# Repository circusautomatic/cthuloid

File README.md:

# cthuloid

Cthuloid is an experimental autonomous theater umbrella project by Circus Automatic.

build a theater system that integrates robotics and performance into a hackable physical space where the performer can dictate lighting design to follow their every movement. Future plans include sound integration, shape changing scenery and more.

Inspired largely by video game level design, it will use blender and other programs for its internal representation. low cost electronics / sensors will be crafted for its real world implementation. a big goal is to form the feedback loop which will allow for more dynamic performance possibilities.
---

Folders of note:
- ### LightArm 
*-ethernet-enabled spotlight robot project*
- ### Arduino/LightArm 
*-firware for the spotlight robot*
- ### Arduino/LEDController  
*-firmware for ethernet-enabled controller for LEDs at high resolution*
- ### ghettopticon 
*-humanoid robot mounted on a motorized wheelchair (should be moved to its own repo)*

## License

Not yet declared.

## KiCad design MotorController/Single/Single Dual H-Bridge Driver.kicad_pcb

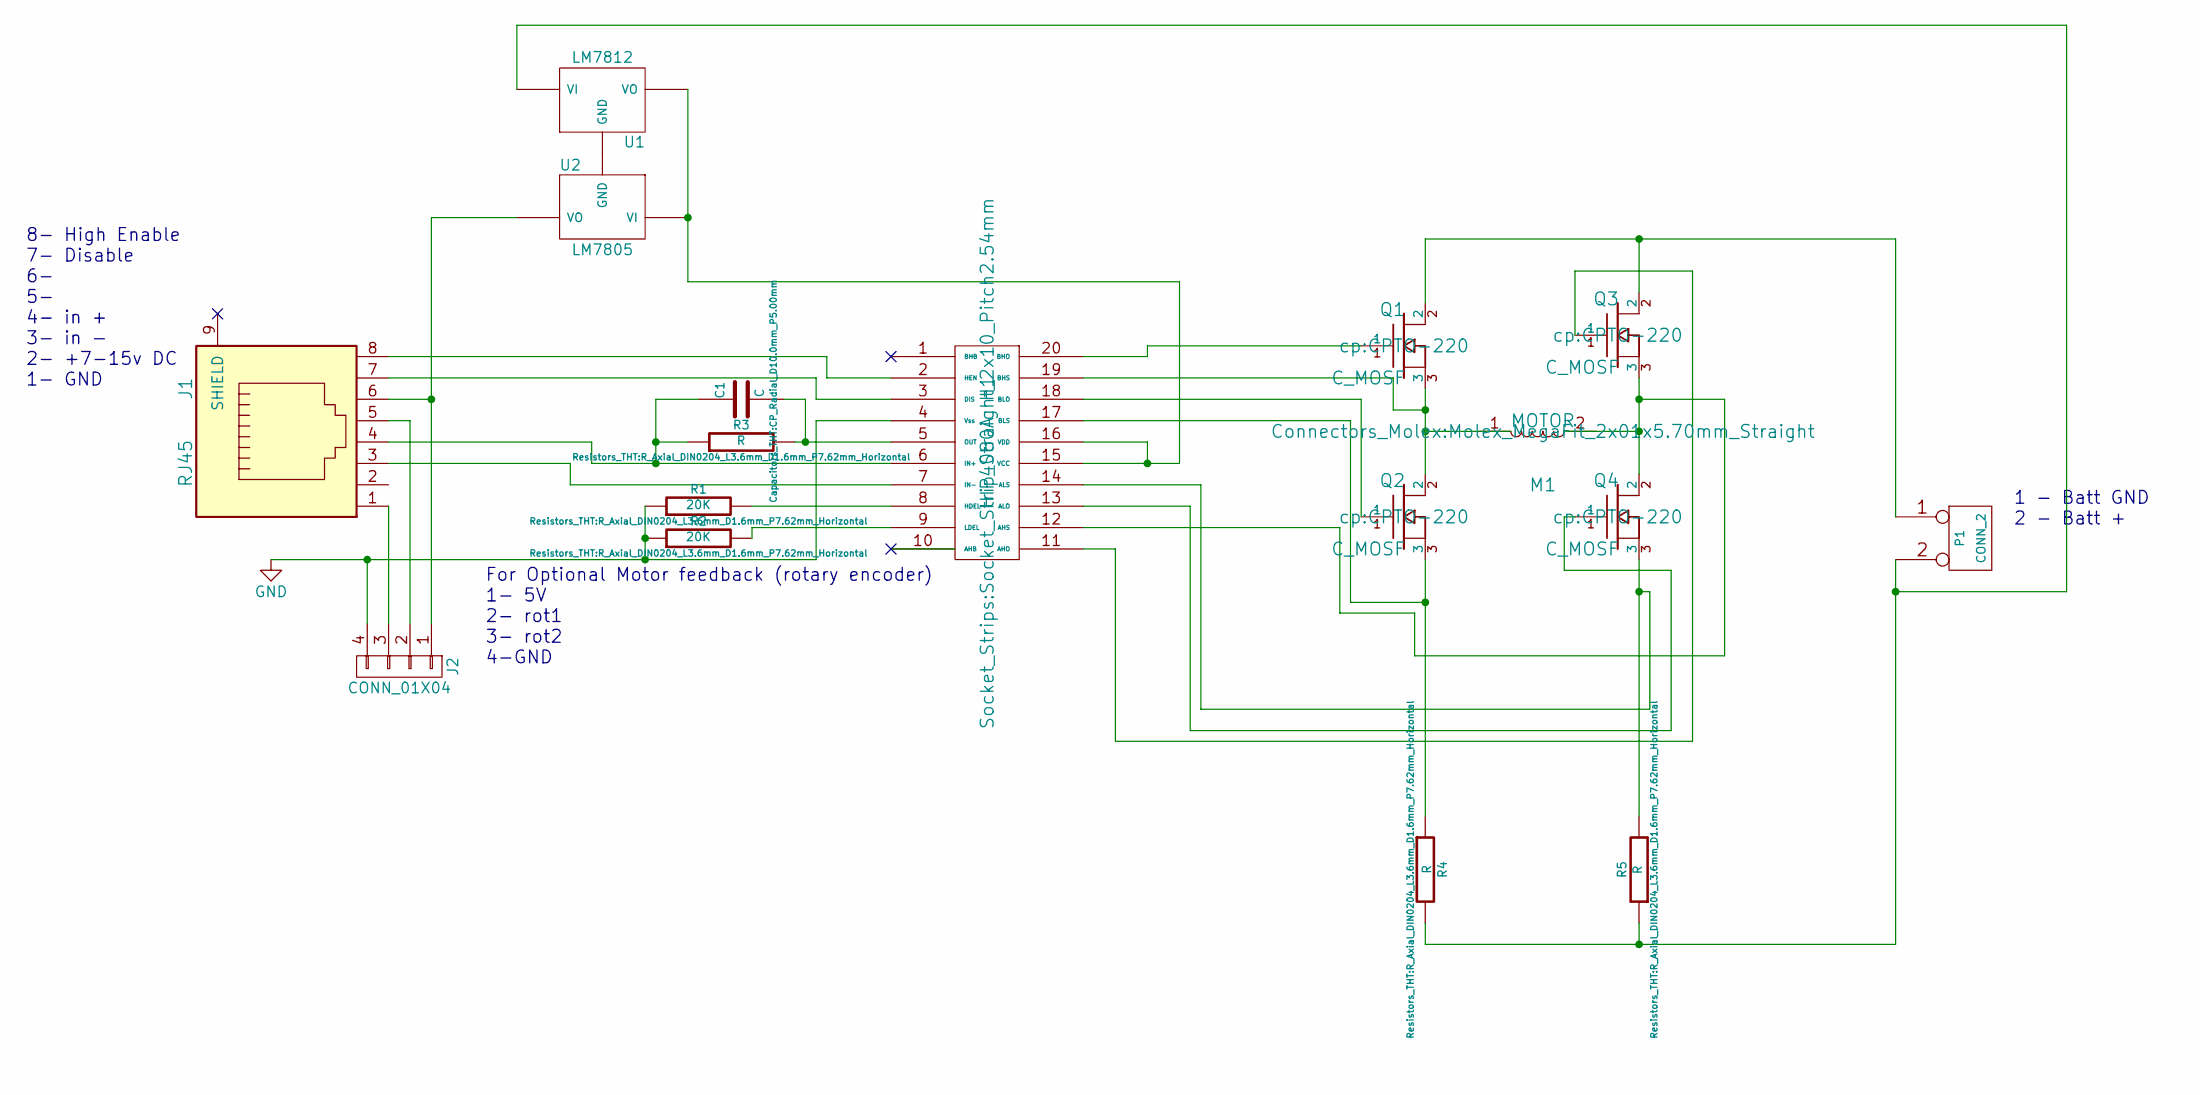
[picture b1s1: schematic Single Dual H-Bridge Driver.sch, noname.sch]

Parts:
C1: C; CP_Radial_D10.0mm_P5.00mm
H1: HIP4080A; Socket_Strip_Straight_2x10_Pitch2.54mm
J1: RJ45; RJ45_8
J2: CONN_01X04; JST_EH_B04B-EH-A_04x2.50mm_Straight
M1: MOTOR; Molex_MegaFit_2x01x5.70mm_Straight
P1: CONN_2; Molex_MegaFit_2x01x5.70mm_Straight
Q1, Q2, Q3, Q4: C_MOSF; CPTO-220
R1, R2: 20K; R_Axial_DIN0204_L3.6mm_D1.6mm_P7.62mm_Horizontal
R3, R4, R5: R; R_Axial_DIN0204_L3.6mm_D1.6mm_P7.62mm_Horizontal
U1: LM7812; CPTO-220
U2: LM7805; CPTO-220

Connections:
GND: H1.4 (Vss), J2.4, R1.1, R2.1
unnamed: C1.1, H1.6 (IN+), J1.4, R3.1
unnamed: C1.2, H1.5 (OUT), R3.2
unnamed: H1.2 (HEN), J1.8
unnamed: H1.3 (DIS), J1.7
unnamed: H1.7 (IN-), J1.3
unnamed: H1.8 (HDEL), R1.2
unnamed: H1.9 (LDEL), R2.2
unnamed: H1.11 (AHO), Q3.1
unnamed: H1.12 (AHS), M1.2, Q3.3, Q4.2
unnamed: H1.13 (ALO), Q4.1
unnamed: H1.14 (ALS), Q4.3, R5.2
unnamed: H1.15 (VCC), H1.16 (VDD), U1.VO, U2.VI
unnamed: H1.17 (BLS), Q2.3, R4.1
unnamed: H1.18 (BLO), Q2.1
unnamed: H1.19 (BHS), M1.1, Q1.3, Q2.2
unnamed: H1.20 (BHO), Q1.1
unnamed: J1.1, J2.3
unnamed: J1.5, J2.2
unnamed: J1.6, J2.1, U2.VO
unnamed: P1.1, Q1.2, Q3.2
unnamed: P1.2 (PM), R4.2, R5.1, U1.VI
unnamed: U1.GND, U2.GND

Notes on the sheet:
8- High Enable 7- Disable 6- 5- 4- in + 3- in - 2- +7-15v DC 1- GND
1 - Batt GND 2 - Batt +
For Optional Motor feedback (rotary encoder) 1- 5V 2- rot1 3- rot2 4-GND

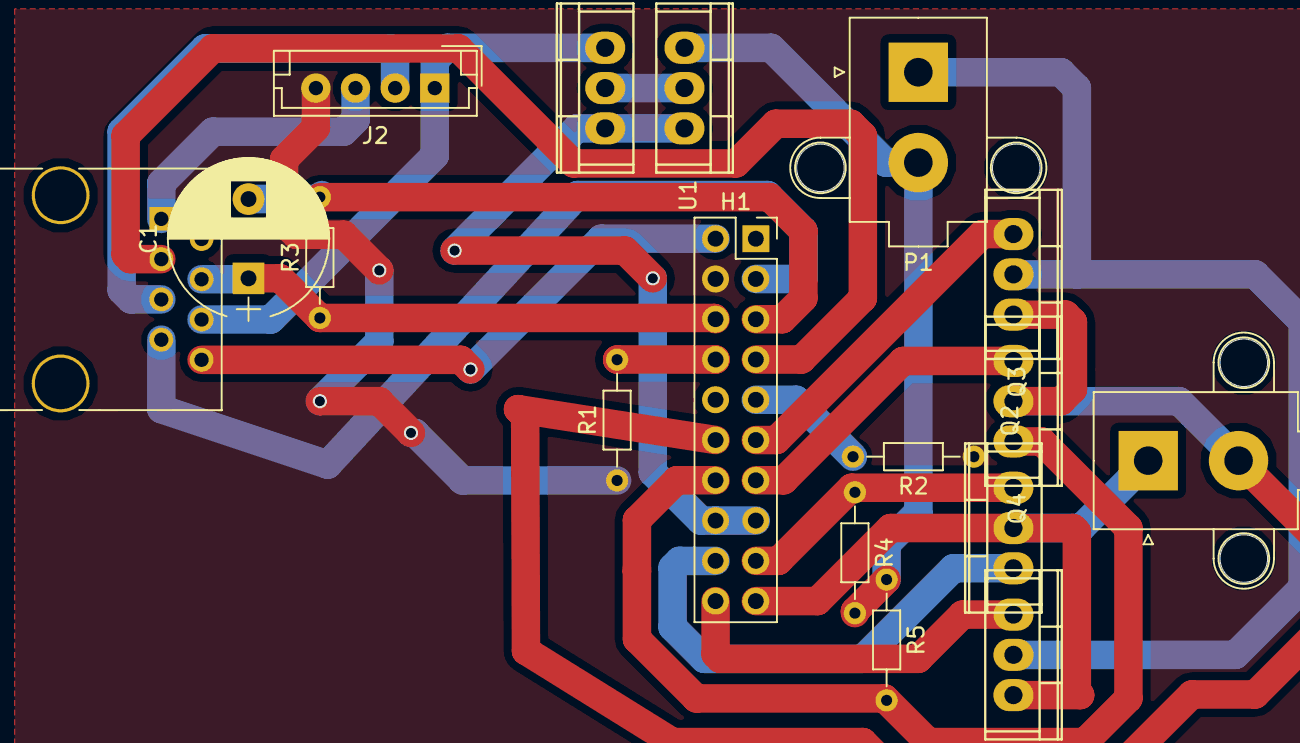
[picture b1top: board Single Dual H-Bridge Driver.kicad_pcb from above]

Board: 2 copper layers, 17 parts (0 on the bottom side), 23 nets.

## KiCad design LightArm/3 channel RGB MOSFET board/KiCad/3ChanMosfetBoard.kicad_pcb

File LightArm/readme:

An ethernet-enabled LED spotlight robot with Dynamixel servos and 3D printed parts.

The controller for this robot listens for TCP/IP connections on port 1337, supports multiple connections, and speaks a human-readable protocol with instructive error messages. It runs on an Arduino Mega and communicates with Dynamixel servos via USART.

Blender is used as a modeling and simulation environment. The robot can be animated or controlled in real-time. To do this, you must put the IP address of the robot in the model name, run the robot_panel.py script, and then turn Animation mode.

Controlling the robot is as simple as telneting to it. IP properties are settable and stored in EEPROM. Mac address is assigned based on the IP address. DHCP is not supported only because of the difficulties of not using static IPs.

In this repo:
android - a simple android program to control movement of two LightArms
blender - Blender models and python integration for controlling LightArms
python - useful standalone scripts
LED MOSFET board.fzz - a schematic of the LED driver

(firmware is located in /Arduino)

Components:
- 2 Dynamixel servos
- 100 Watt LED, heatsink, and fan
- custom LED driver
- Arduino Mega and ethernet module
- 12 Volt power supply (Wattage?)
- step-up power converter (to 33 Volts)

Getting Started:
- telnet to the lightarm on port 1337. Default IPv4 address is 10.0.2.255; see /Arduino/LightArm/LightArm.ino. There is no greeting upon connection, due to the nature of the Arduino ethernet library. Once connected, type the following commands and hit enter after each one.
- r
- p <1-5>
- pwm <0-65535>

Commands:
plevel - see or change the amount of text sent in response to a command
pwm - change LED brightness
v - check first servo voltage
r - report servo positions
s - change servo positions
p - choose preset position of servos
speed - see or change servo speed
relax - relax servos so they can be manually positioned
torq - un-relax some or all servos
circle - perform a circle in the plane perpendicular to neutral
id - change an internal servo ID
ip - change static IP address
gateway - change gateway address
port - change listening port
restart - restart network module to use new settings
clear - clear saved settings (just network settings for now)

TODO:
- modify ethernet library to greet client upon connection
- support DHCP and figure out how to identify individual robots
- add option for network security (so a person cannot just telnet into the robot)

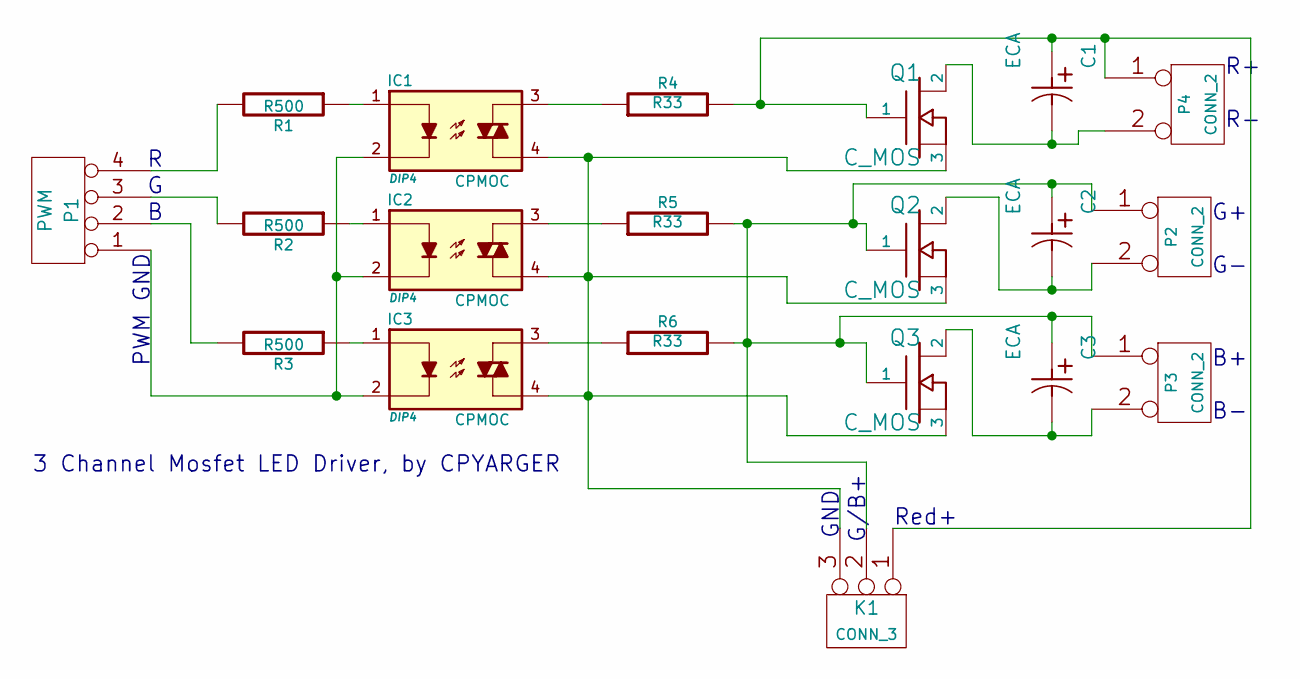
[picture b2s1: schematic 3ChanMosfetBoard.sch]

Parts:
C1, C2, C3: ECA
IC1, IC2, IC3: CPMOC; DIP4
K1: CONN_3
P1: PWM
P2, P3, P4: CONN_2
Q1, Q2, Q3: C_MOS
R1, R2, R3: R500
R4, R5, R6: R33

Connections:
unnamed: C2.2, P2.2 (PM), Q2.2
unnamed: C3.2, P3.2 (PM), Q3.2
unnamed: C1.2, P4.2 (PM), Q1.2
unnamed: IC2.1, R2.1
unnamed: IC3.1, R3.1
unnamed: IC1.1, R1.1
unnamed: IC1.3, R4.1
unnamed: IC1.2, IC2.2, IC3.2, P1.1
unnamed: IC2.3, R5.1
unnamed: IC3.3, R6.1
unnamed: C2.1, C3.1, K1.2 (PM), P2.1, P3.1, Q2.1, Q3.1, R5.2, R6.2
unnamed: C1.1, K1.1, P4.1, Q1.1, R4.2
unnamed: P1.2, R3.2
unnamed: P1.3, R2.2
unnamed: P1.4, R1.2
unnamed: IC1.4, IC2.4, IC3.4, K1.3, Q1.3, Q2.3, Q3.3

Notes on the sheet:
GND
Red+
G/B+
PWM GND
3 Channel Mosfet LED Driver, by CPYARGER

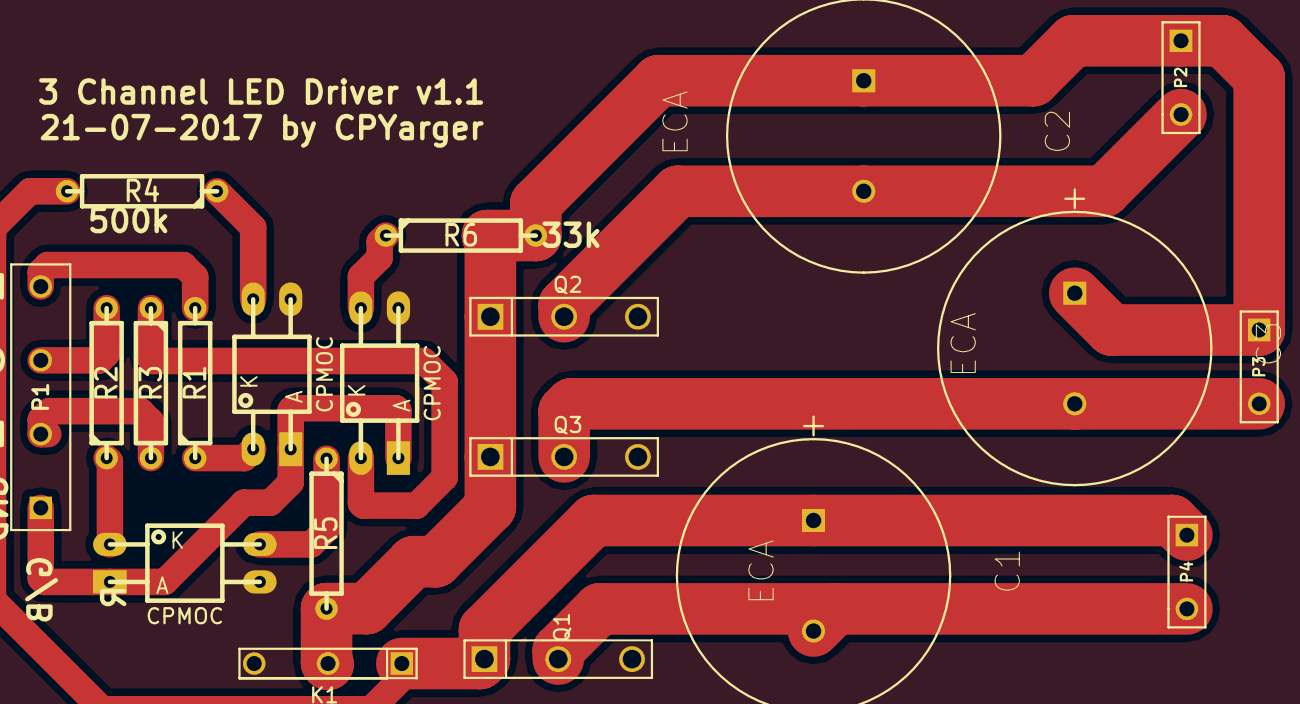
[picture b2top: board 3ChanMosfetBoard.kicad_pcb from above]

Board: 2 copper layers, 20 parts (0 on the bottom side), 16 nets.

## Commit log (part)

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2016-03-24 android app to control light arms
2016-03-25 demo app
2016-06-07 adding in models
2016-06-07 reorg
2016-06-08 adding in ik axis constraints to bones, and also a new bone for the ik which is a target bone, also a track to constraint and a location constraint on the target bone for the ik chain so that it all 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
2016-06-09 voyeur handler to watch arm
2016-06-09 added some cubes driven by the rotation of the bones to hack together getting rotation values
2016-06-09 adding in some empties for an experiment that is currently not working
2016-06-09 print euler angles correctly
2016-06-09 both angles constrained to 0-180
2016-06-09 sending network commands
2016-06-09 correct angle calc
2016-06-09 pwm fade network test
2016-06-09 map light intensity
2016-06-09 improve pwm fade script
2016-06-13 increase pwm max
2016-06-25 fading control program
2016-06-25 smooth fade
2016-06-25 two lights tied together
2016-06-30 robot panel for saving and loading
2016-07-01 blender control of static lights
2016-07-06 clean up
2016-07-06 improve perform, fade, and server scripts
2016-07-06 replaced cylinder model with box model
2016-07-11 correct rotation calc; to_euler no longer freaks out
2016-07-12 fix bones
2016-07-12 adding in gymbal model blend file
2016-07-13 gimbal arm angles have couple issues
2016-07-14 adjust angle calculation
2016-07-14 import ghettopticon and cuemgr
2016-07-15 settable ip in sketch; relative position for gimbal arm targeting; move Arduino folder
2016-07-17 new range to fade script
2016-07-17 test sketch for setting servo compliance slope
2016-08-05 can set compliance; enable eeprom save/load ip settings
2016-08-16 remove explicit mac address; clear settings command
2016-08-18 add second high freq PWM channel to LEDController
2016-08-18 config cue manager for IP devices
2016-08-20 save and load cues
2016-08-20 fade. adjust range
2016-08-20 scenes and cuesheet
2016-08-20 hack for double overhead LED
2016-09-17 adding in vrav to credits
2016-11-23 adding in a robotarm3.blend and arm-model-detail.blend for better visualization
2016-11-23 adding in test cutesy anim
2016-11-23 saving some file settings
2016-12-09 messing around with the fritzing file
2017-02-05 documentation. handle cue file errors gracefully
2017-02-05 Rename example_cue.py to example.cue
    rename
2017-02-05 Create README.md
    root readme
2017-02-05 note on the library folder
2017-02-05 readme and folder renames
2017-02-05 moved orphaned file
2017-02-05 LightArm readme
2017-02-05 documentation
2017-02-05 add dummy eeprom commands for serial mode. use new PWM library for all PWM pins. documentation
2017-03-22 initial attempt at tech demo anim
2017-03-23 fix to compile in serial mode
2017-03-23 add compliance; move speed to top of file
2017-03-23 update animation and animate LED
2017-03-23 attempt to make anim more sweeping
2017-03-29 add getting started to readme
2017-04-04 adding a super basic armature, for great testing
2017-04-04 cement orientation; add labels showing direction of servo labels
2017-04-04 correct animation orientation
2017-05-01 add Conceptinetics DMX sketches
2017-05-02 create dmx led controller sketch
2017-05-03 add extra pins; remove other DMX sketch
2017-05-03 change pins back because of weirdness
2017-06-09 update starting angles
2017-06-09 initial test for prinboo model
2017-06-20 control 4 PWM channels at 16-bit resolution via two different methods
2017-06-20 serial sketch with human readable protocol for Prinboo's head and arms
2017-06-21 adafruit pwm servo driver library
2017-06-22 udev rules for Prinboo arduinos
2017-06-23 merging in comments left on my laptop about lightarm angles calculation
2017-06-24 work in progress for hamburger cat
2017-06-25 separate file for prinboo objects
2017-06-25 fix readings text
2017-06-25 update prinboo controls
2017-06-25 prinboo.py compiles
2017-06-25 comments
2017-06-25 turn on dmx and turn off lightarms
2017-06-25 fixes for prinboo motors
2017-06-25 prinboo view
2017-06-25 load and save commands work for prinboo poses
2017-06-25 update prinboo animation export script
2017-06-25 exported prinboo pose test
2017-06-25 scenes and cues for prinboo
2017-06-25 restored DMX fading; program plays nice when OLA is missing
2017-06-25 shell script for prinboo host
2017-06-25 adding in facial animation blend + test file
2017-06-26 orient face upright
2017-06-26 adding non talking facial animation
2017-06-26 talk to prinboo over sockets and ssh
2017-06-27 prinboo pose-to-pose animation
2017-06-27 network communication with prinboo working
2017-06-27 basic poses and calibrate arduino sketches
2017-06-27 video playback
2017-06-28 Update prinboo.py
    turn off prinboo print statements
2017-06-28 list cue commands once; remove unnecessary cmds
2017-06-28 fix directions; remove more prints
2017-06-28 prinboo random motions
2017-06-28 replace video cmd with live keys; can drive prinboo from any screen
2017-06-28 rename talking video file; split out prinboo socket scripts
2017-06-28 fix keyboard controls
2017-06-29 motor requires heartbeat; adjust face starting angle
2017-07-07 animating limbs from single cue--needs cleanup
2017-07-08 disable servo 5 because it broke. update animation to compensate
2017-07-09 turn off print statement
2017-07-17 flipped version of modular led circuit
2017-07-18 adding in chris yarger's rgb pcb design
2017-07-26 second DMX LED controller with consistent lighting behavior
2017-08-10 Chris's updates
2017-08-10 cleanup
2017-08-10 add gitignore
2017-08-19 update light and motor boards
2017-08-19 update light board
2017-09-14 added RGB channels to cuemgr
2017-09-16 adding in rgb_led_controller code written by frank
2017-09-27 adding in changes
2017-09-29 update for new RGB controller
2018-03-22 updating various changes in codebase , adding in new esp32 directory for code running on the esp32
2018-03-22 adding in esp32 directory , again with feeling
2018-03-22 removing badly named directory
2018-03-22 fixing more bad file names
2018-03-22 adding in directory esp32
2018-03-22 just a hotfix
    allowing for more red channels.
2018-03-25 adding in 12 channel version of 32wifi
2018-03-26 default light pwm setings
2018-03-26 get er done
2018-04-12 comitting in some tweaks to the esp32 light sketch that frank did
2018-04-13 stashing this
2018-04-14 singleton was being init twice
2018-04-15 add UI 12 channels BGR per board
2018-05-06 fading both DMX and lightarms. setup config using __new__
2018-05-07 video cue using paramiko
2018-05-07 turn off prinboo key bindings
2018-05-29 quad-BGR lights in blender
2018-05-30 fixing connection issue
2018-06-08 adding quad-light blend
2018-09-16 Update README.md
    just a spelling fix
2018-09-26 adding example exp32 artnet fastled sketch
2018-10-05 adding new sketch based off of 32wifi12frak, will add neopixel functionality to existing code
2018-10-05 more clean up
2018-10-05 some more cleanup
2018-10-05 adding in pcb designs
2018-11-17 markdown test
2018-11-17 fast led stubs
2018-12-12 adding in frank's interpolation code
2018-12-12 adding in new sketch fleeky cleaned up and ash added actual real code to
2018-12-13 adding in control over a whole strip's rgb, thanks to frank and ashes
2018-12-14 adding a fade-up example
2018-12-23 adding individual led control function
2019-01-11 adding ethernet breakout pcb
2019-01-12 adding in correct breakout board
2019-01-13 adding in rgb-strip.blend and .py
2019-01-13 adding in rgb_multistrip.blend
2019-01-13 fixing order issues
2019-01-13 added cmdMultiMultiColor mm
2019-01-14 removed debug statements, adjusted tick timing
2019-02-03 zorko made macro version of min function
2019-02-03 added mm command for light control
2019-02-08 adding in white/rgb light control example
2019-03-04 added pwm2 command that allows the specification of numPeriods on the command line
2019-04-14 adding in initial rotary encoder sketch
2019-04-15 lightswitch proof of concept
2019-06-28 adding in work files from last show
2020-02-27 Updated for ESP8266 controller
